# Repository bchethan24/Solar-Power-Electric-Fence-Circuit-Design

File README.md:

# Solar Powered Electric Fence Circuit

*A high-voltage, renewable energy-based perimeter security system using CD4047 pulse generation and MOSFET power switching.*

---

## Overview

This project features a fully custom-built **Solar Powered Electric Fence**, designed to deliver controlled, safe high-voltage pulses for agricultural and perimeter protection. It integrates a solar charging system with a battery backup to ensure 24/7 off-grid operation without reliance on the power grid.

---

## System Architecture
```
┌────────────────────────────┐       ┌────────────────────────────┐
│   Solar Charging Stage     │       │   Pulse Generation Stage   │
│ • 12V Solar Panel          │       │ • CD4047 Multivibrator     │
│ • LM317L Voltage Regulator │◄─────►│ • Adjustable Frequency     │
│ • 12V 7Ah Battery Storage  │       │ • 46 Hz – 58 Hz Range      │
└────────────────────────────┘       └─────────────┬──────────────┘
                                                   │
                                                   ▼
┌────────────────────────────┐       ┌────────────────────────────┐
│   High-Voltage Stage       │       │      Switching Stage       │
│ • Step-up Transformer      │◄─────►│ • Dual IRF3205 MOSFETs     │
│ • High-Voltage Pulse Out   │       │ • High-Current Handling    │
│ • Safe Deterrent Shocks    │       │ • Low-Loss Power Switching │
└────────────────────────────┘       └────────────────────────────┘
```

## ⚙ Working Principle

1. **Energy Harvesting:** The solar panel generates DC power, which is regulated by the **LM317L** to provide a constant charging voltage to the **12V 7Ah Lead-Acid battery**.
2. **Pulse Timing:** A **CD4047 IC** is configured in astable mode to produce a continuous square wave. The frequency is adjustable (**46–58 Hz**) via a variable resistor to fine-tune the deterrent intensity.
3. **Power Switching:** The logic-level signal from the IC drives the gates of two **IRF3205 MOSFETs**. These MOSFETs switch the battery current through the primary winding of the transformer.
4. **Inductive Boost:** The **Step-up Transformer** converts the low-voltage switched DC into high-voltage, short-duration pulses suitable for long-distance fencing wires.

---

## 🧩 Detailed Hardware Information

### 🧮 Pulse Generation (CD4047)
The timing is governed by the RC network connected to the astable multivibrator pins.

| Component | Value | Function |
| :--- | :--- | :--- |
| **Resistor (R)** | 390 kΩ + 100 kΩ Pot | Frequency Tuning |
| **Capacitor (C)** | 10 nF | Timing Constant |
| **Pulse Period (T)** | 17.16 – 21.56 ms | T = 4.4RC |
| **Frequency (f)** | 46 Hz – 58 Hz | Output Pulse Rate |

### 🔋 Power & Switching
| Component | Specification | Role |
| :--- | :--- | :--- |
| **Voltage Regulator** | LM317L | Battery Charge Control |
| **Storage** | 12V, 7Ah Battery | Lead-Acid Energy Storage |
| **Switching MOSFET** | IRF3205 | High-Current Driver ($V_{DSS}=55V$) |
| **Protection** | Schottky Diodes | Reverse Polarity & Surge Protection |

---

## 📐 Design Features

* **Fully Custom Design:** Optimized schematics and PCB layouts specifically for high-current pulse switching.
* **Off-Grid Optimized:** Designed for outdoor operation with minimal maintenance.
* **Safety Integrated:** Intermittent pulse generation ensures shocks are deterrent but safe for livestock and humans.
* **Modular Layout:** Segmented circuit stages for charging, control, and high-voltage output for easier troubleshooting.

---

## 📂 Repository Contents
- `/hardware`: Schematics, PCB layouts and 3D PCB layout visualizations.
- `/docs`: component datasheets and project report.
- `/manufacturing`: Gerber files of the PCB layouts.

---

## 🧠 Learning Outcomes
- Designing **Battery Charging Circuits** with voltage regulation.
- Implementing **Astable Multivibrators** for precise signal timing.
- Managing **High-Voltage switching** 
- Integrating **Renewable Energy** into practical security applications.

---

## 🧾 License
**MIT License** Permission is granted to use, modify, and distribute under MIT terms.

---

## ✅ Summary
A robust, solar-powered security solution that demonstrates the practical application of **Power Electronics** and **Analog Design**. The system provides a sustainable, cost-effective deterrent for livestock and perimeter management, verified through rigorous testing and custom PCB fabrication.

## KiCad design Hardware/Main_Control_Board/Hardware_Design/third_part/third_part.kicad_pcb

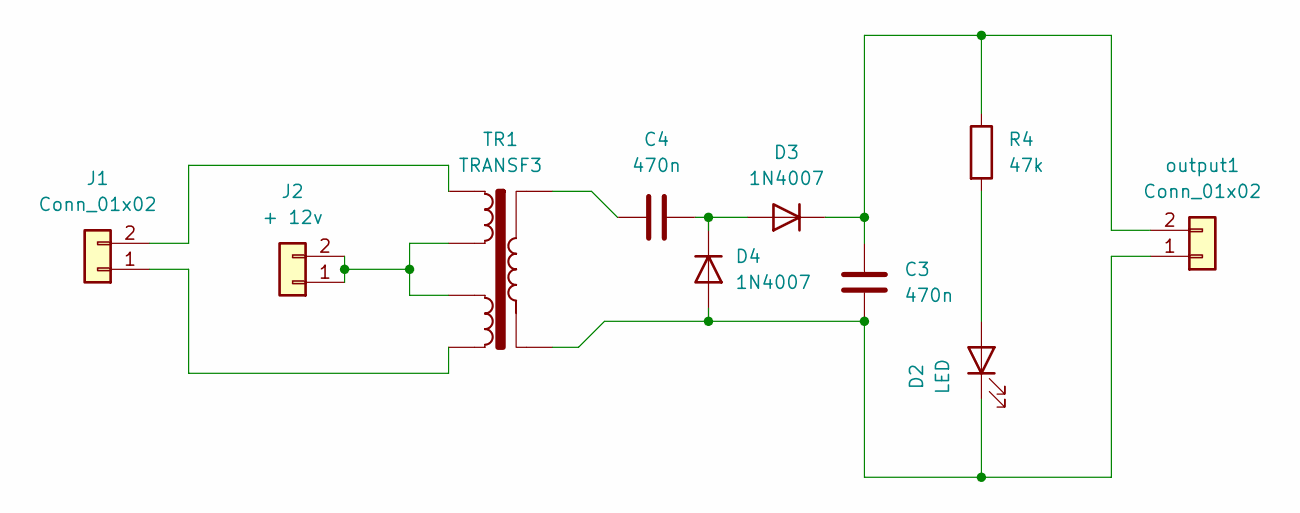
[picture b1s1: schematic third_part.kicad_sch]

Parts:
C3, C4: 470n; C_Axial_L3.8mm_D2.6mm_P7.50mm_Horizontal
D2: LED; LED_D1.8mm_W1.8mm_H2.4mm_Horizontal_O1.27mm_Z1.6mm
D3, D4: 1N4007; D_DO-41_SOD81_P10.16mm_Horizontal
J1: Conn_01x02; PhoenixContact_GMSTBA_2,5_2-G-7,62_1x02_P7.62mm_Horizontal
J2: + 12v; PhoenixContact_GMSTBA_2,5_2-G-7,62_1x02_P7.62mm_Horizontal
R4: 47k; R_Axial_DIN0207_L6.3mm_D2.5mm_P10.16mm_Horizontal
TR1: TRANSF3; Transformer_Myrra_EI30-5_44000_Horizontal ( self made )
output1: Conn_01x02; PhoenixContact_GMSTBA_2,5_2-G-7,62_1x02_P7.62mm_Horizontal

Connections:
unnamed: C4.2, TR1.1
unnamed: D2.2 (A), R4.2
unnamed: C3.2, D2.1 (K), D4.2 (A), TR1.2, output1.1
unnamed: C4.1, D3.2 (A), D4.1 (K)
unnamed: C3.1, D3.1 (K), R4.1, output1.2
unnamed: J1.1, TR1.6
unnamed: J1.2, TR1.3
unnamed: J2.1, J2.2, TR1.4, TR1.5

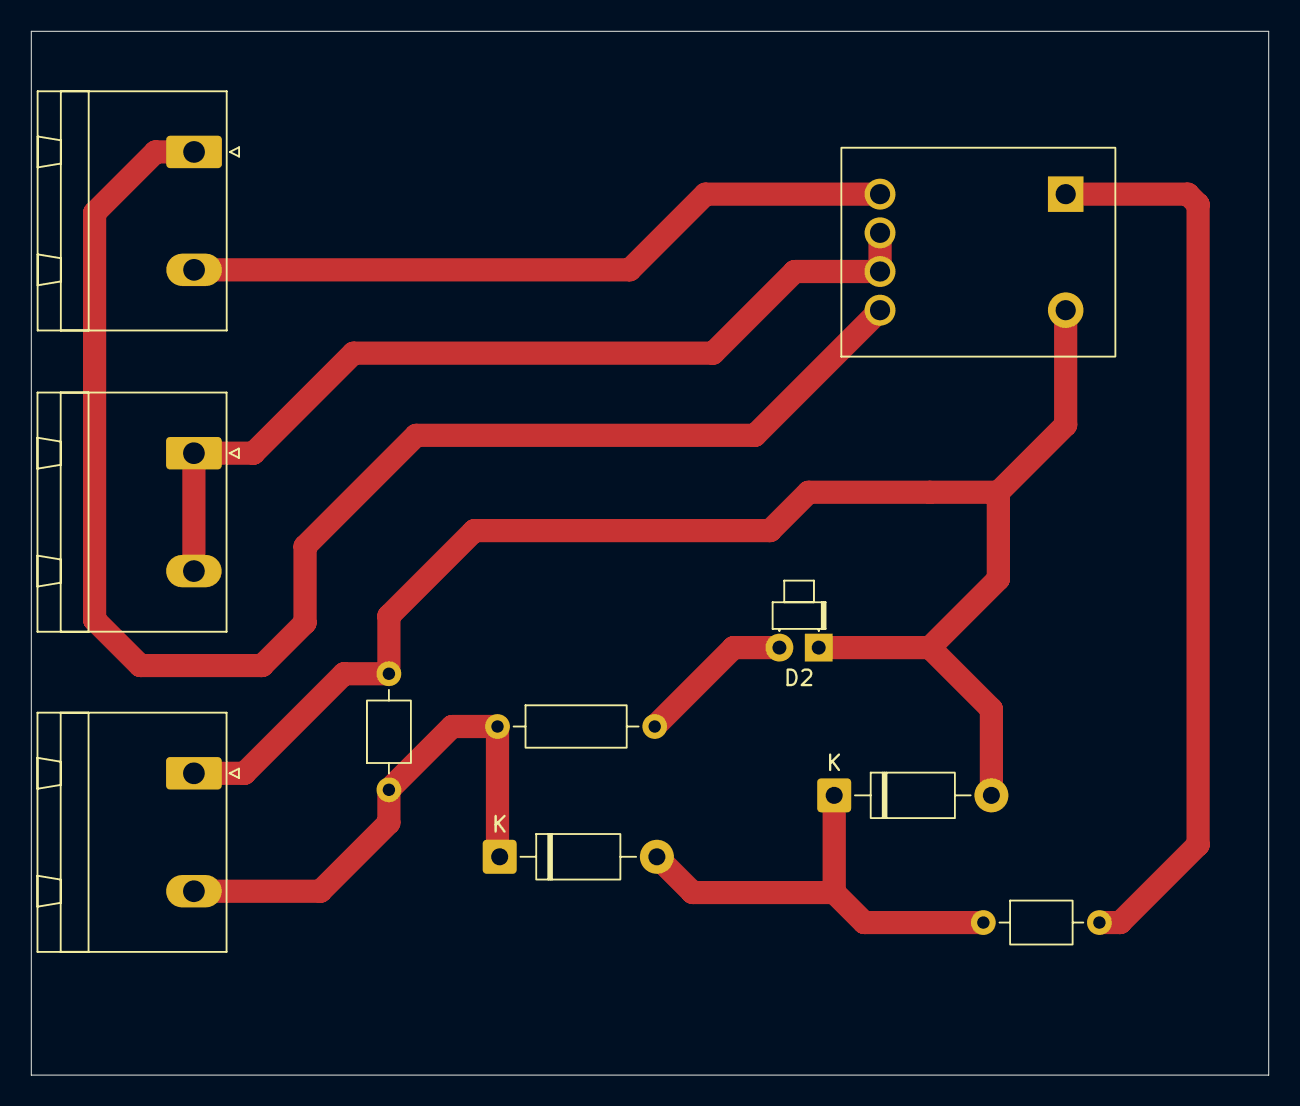
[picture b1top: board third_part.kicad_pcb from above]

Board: 2 copper layers, 80.0 x 67.5 mm, 10 parts (0 on the bottom side), 8 nets.

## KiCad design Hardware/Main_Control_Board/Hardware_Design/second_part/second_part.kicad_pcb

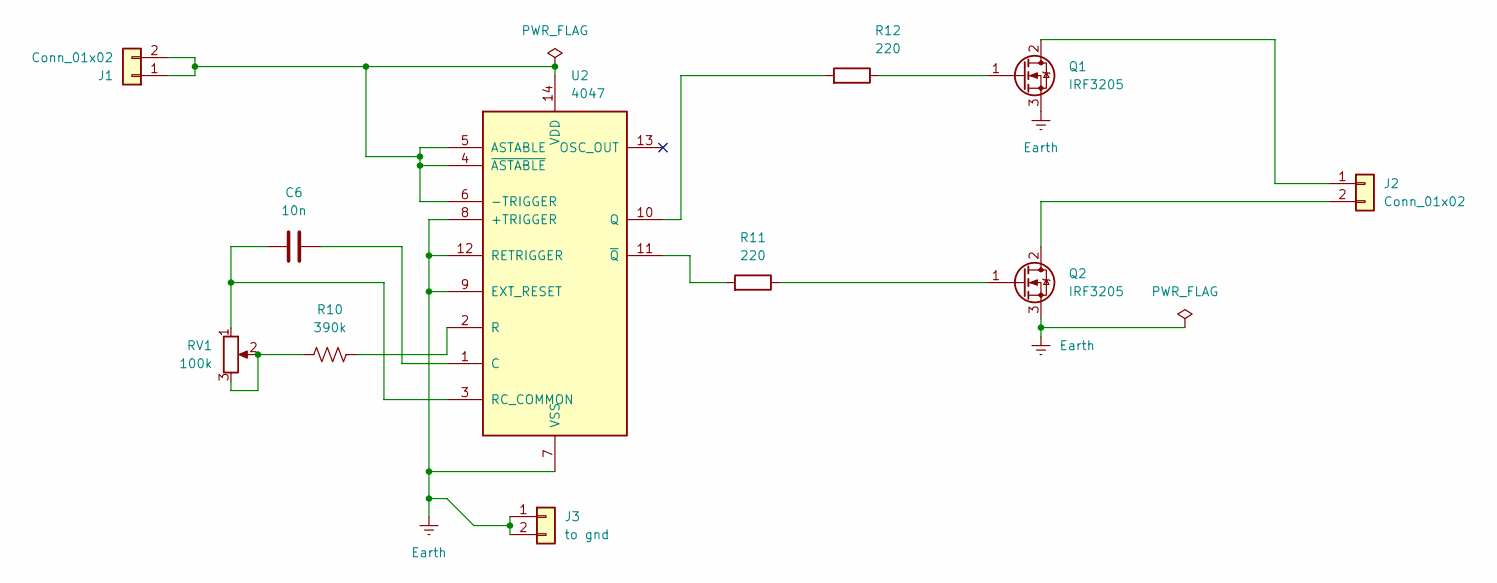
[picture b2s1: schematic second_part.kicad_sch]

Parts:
C6: 10n; C_Axial_L3.8mm_D2.6mm_P7.50mm_Horizontal
J1, J2: Conn_01x02; PhoenixContact_GMSTBA_2,5_2-G-7,62_1x02_P7.62mm_Horizontal
J3: to gnd; PhoenixContact_MSTBA_2,5_2-G-5,08_1x02_P5.08mm_Horizontal
Q1, Q2: IRF3205; TO-220-3_Vertical
R10: 390k; R_Axial_DIN0207_L6.3mm_D2.5mm_P10.16mm_Horizontal
R11, R12: 220; R_Axial_DIN0207_L6.3mm_D2.5mm_P10.16mm_Horizontal
RV1: 100k; Potentiometer_Bourns_3386W_Horizontal
U2: 4047; DIP-14_W7.62mm_Socket_LongPads

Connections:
Earth: J3.1, J3.2, Q1.3 (S), Q2.3 (S), U2.7 (VSS), U2.8 (+TRIGGER), U2.9 (EXT_RESET), U2.12 (RETRIGGER)
unnamed: J1.1, J1.2, U2.4 (~ASTABLE), U2.5 (ASTABLE), U2.6 (-TRIGGER), U2.14 (VDD)
unnamed: J2.1, Q1.2 (D)
unnamed: J2.2, Q2.2 (D)
unnamed: Q1.1 (G), R12.1
unnamed: Q2.1 (G), R11.1
unnamed: R10.1, RV1.2, RV1.3
unnamed: C6.2, U2.1 (C)
unnamed: R12.2, U2.10 (Q)
unnamed: R10.2, U2.2 (R)
unnamed: C6.1, RV1.1, U2.3 (RC_COMMON)
unnamed: R11.2, U2.11 (~Q)

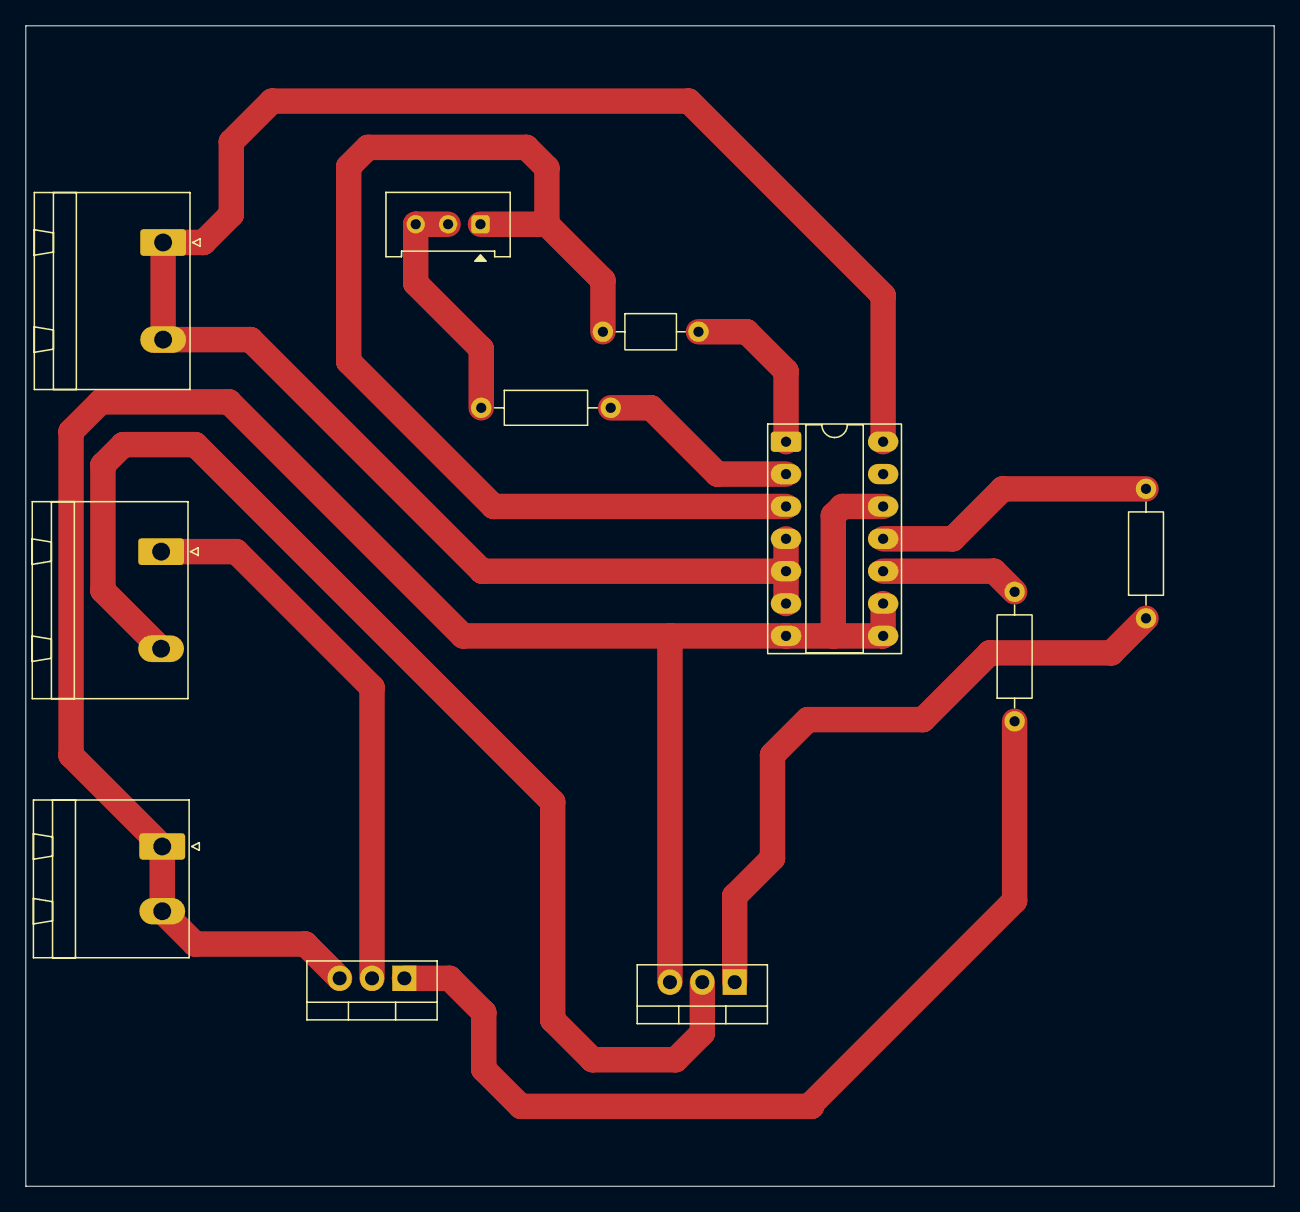
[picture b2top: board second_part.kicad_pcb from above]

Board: 2 copper layers, 98.0 x 91.1 mm, 11 parts (0 on the bottom side), 12 nets.

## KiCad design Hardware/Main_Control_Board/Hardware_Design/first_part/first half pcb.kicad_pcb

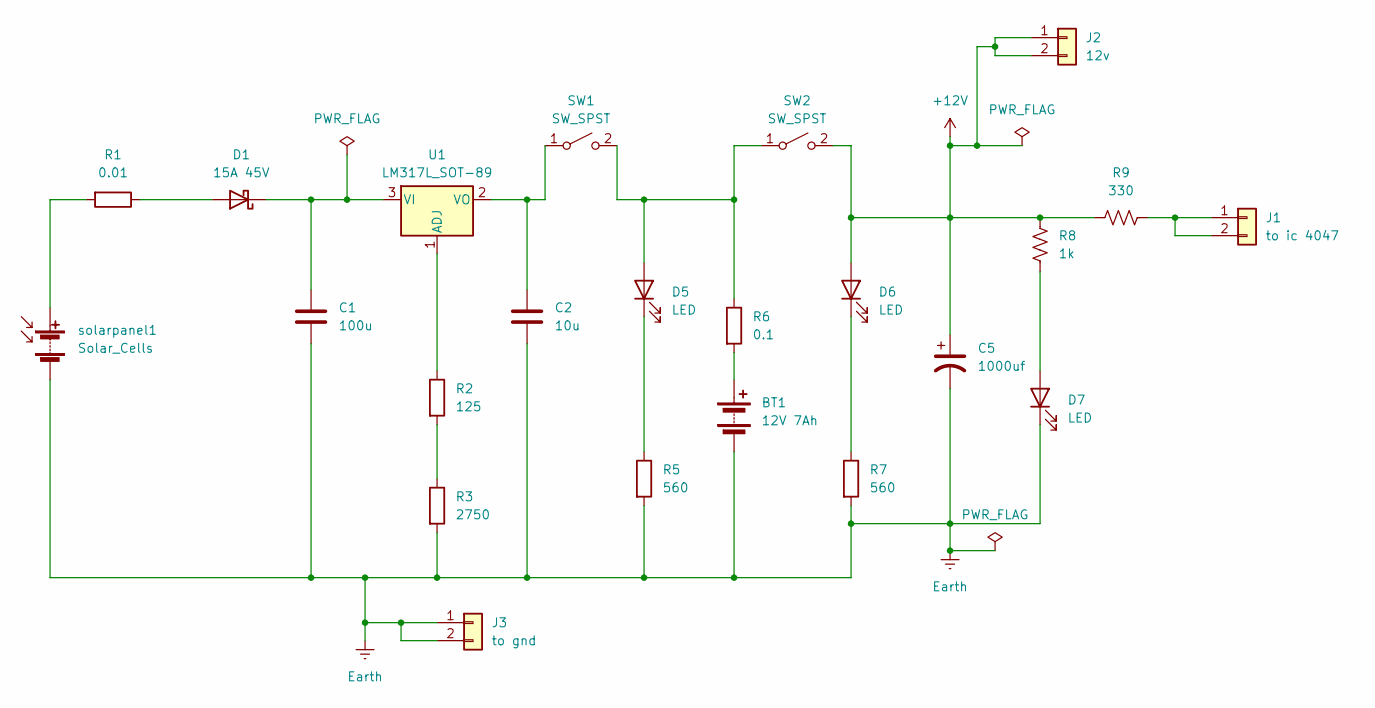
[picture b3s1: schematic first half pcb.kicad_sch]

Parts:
BT1: 12V 7Ah; PhoenixContact_GMSTBA_2,5_2-G-7,62_1x02_P7.62mm_Horizontal
C1: 100u; C_Axial_L3.8mm_D2.6mm_P7.50mm_Horizontal
C2: 10u; C_Axial_L3.8mm_D2.6mm_P7.50mm_Horizontal
C5: 1000uf; CP_Axial_L10.0mm_D4.5mm_P15.00mm_Horizontal
D1: 15A 45V; D_DO-41_SOD81_P10.16mm_Horizontal
D5, D6, D7: LED; LED_D1.8mm_W1.8mm_H2.4mm_Horizontal_O1.27mm_Z1.6mm
J1: to ic 4047; PhoenixContact_MSTBA_2,5_2-G-5,08_1x02_P5.08mm_Horizontal
J2: 12v; PhoenixContact_MSTBA_2,5_2-G-5,08_1x02_P5.08mm_Horizontal
J3: to gnd; PhoenixContact_MSTBA_2,5_2-G-5,08_1x02_P5.08mm_Horizontal
R1: 0.01; R_Axial_DIN0207_L6.3mm_D2.5mm_P10.16mm_Horizontal
R2: 125; R_Axial_DIN0207_L6.3mm_D2.5mm_P10.16mm_Horizontal
R3: 2750; R_Axial_DIN0207_L6.3mm_D2.5mm_P10.16mm_Horizontal
R5, R7: 560; R_Axial_DIN0207_L6.3mm_D2.5mm_P10.16mm_Horizontal
R6: 0.1; R_Axial_DIN0207_L6.3mm_D2.5mm_P10.16mm_Horizontal
R8: 1k; R_Axial_DIN0207_L6.3mm_D2.5mm_P10.16mm_Horizontal
R9: 330; R_Axial_DIN0207_L6.3mm_D2.5mm_P10.16mm_Horizontal
SW1, SW2: SW_SPST; SW_DIP_SPSTx01_Slide_6.7x4.1mm_W7.62mm_P2.54mm_LowProfile
U1: LM317L_SOT-89; TO-220-3_Vertical
solarpanel1: Solar_Cells; PhoenixContact_GMSTBA_2,5_2-G-7,62_1x02_P7.62mm_Horizontal

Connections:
+12V: C5.1, D6.2 (A), J2.1, J2.2, R8.1, R9.1, SW2.2 (B)
Earth: BT1.2 (-), C1.2, C2.2, C5.2, D7.1 (K), J3.1, J3.2, R3.2, R5.2, R7.2, solarpanel1.2 (-)
unnamed: BT1.1 (+), R6.2
unnamed: D1.2 (A), R1.1
unnamed: C1.1, D1.1 (K), U1.3 (VI)
unnamed: D5.2 (A), R6.1, SW1.2 (B), SW2.1 (A)
unnamed: D5.1 (K), R5.1
unnamed: D6.1 (K), R7.1
unnamed: D7.2 (A), R8.2
unnamed: J1.1, J1.2, R9.2
unnamed: R2.2, R3.1
unnamed: C2.1, SW1.1 (A), U1.2 (VO)
unnamed: R2.1, U1.1 (ADJ)
unnamed: R1.2, solarpanel1.1 (+)

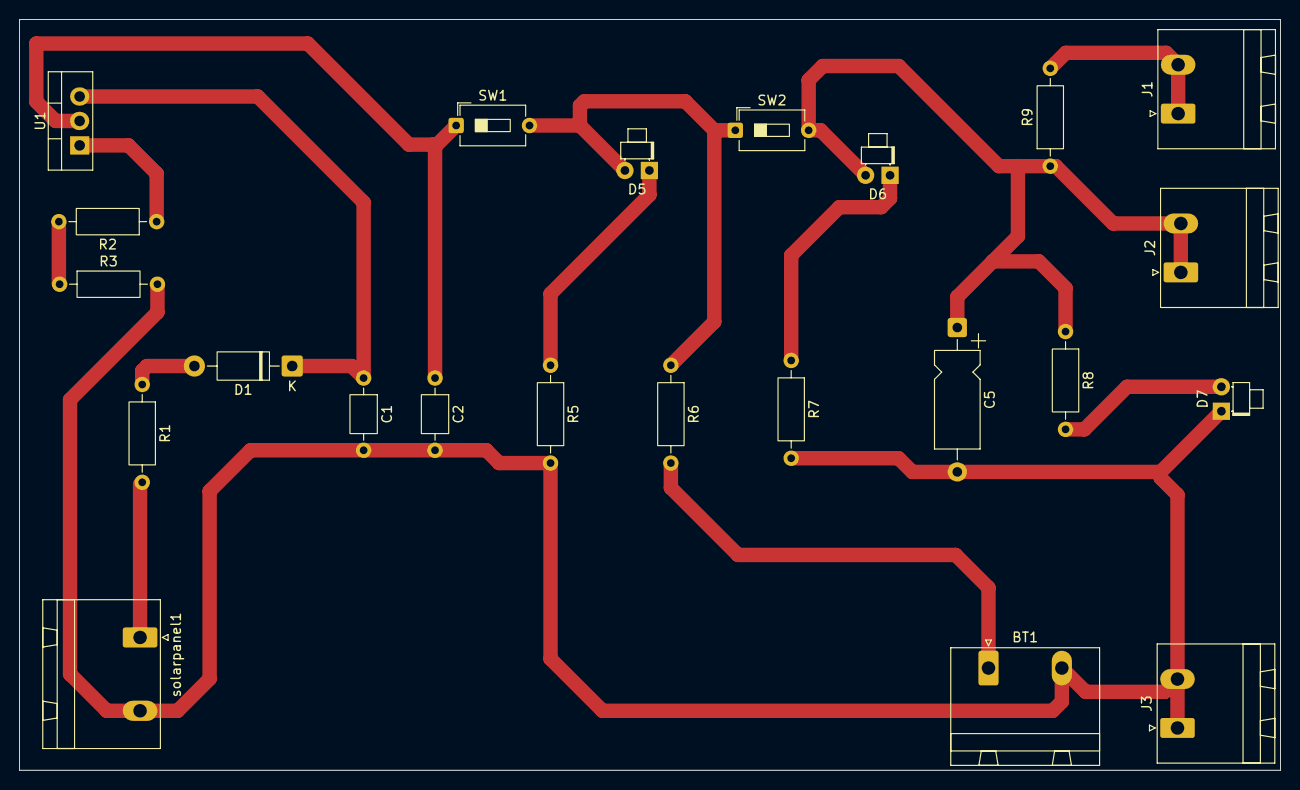
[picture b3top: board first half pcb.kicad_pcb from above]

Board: 2 copper layers, 131.0 x 78.0 mm, 23 parts (0 on the bottom side), 14 nets.

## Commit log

2026-04-26 added printing files in .zip folder
2026-05-02 Simplify README by removing architecture details
    Removed detailed system architecture and project description sections from README.
2026-05-05 Revise design features and repository contents in README
    Updated README to clarify repository contents and design features.
